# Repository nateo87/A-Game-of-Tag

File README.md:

# A Game of Tag
Here's the first genuine game project from David L Heiserman's 1978 book "How to Design & Build Your Own Custom TV Games". It's a very simple game where two player squares are moved around the screen. When one square touches another, both players disappear from the screen (it's up to you to decide who is "it"). Originally even less complex, I opted to add a little beep sound for when the tag occurs. The pitch of the beep can be set with a jumper on the upper-right side of the board.

It's easy for the player charcaters to fly off the screen - I recommend marking on your potentiometer knobs a sort of "starting position". Anyways, I encourage you to take a look into the book and tweak the designs. There's one addition the book recommends that would add "inertia" to the moving squares! Have fun, and please don't hesitate to reach out with questions.

You can just solder wires directly from your player control pots to the PCB, or you can use pinheaders and have wires going from the pots with crimped on molex connectors at the other end. 

<b> BOM </b>

Caps:<br>
100pf x 2<br>
3900pf x 2<br>
10nf x 4<br>
47nf x 2<br>
0.1uf x 9<br>

Elec. Caps:<br>
1uf x 2<br>
10uf x 1<br>

Resistors:<br>
470ohm x 4<br>
2.2k x 1<br>
3.3k x 2<br>
22k x 1<br>
33k x 2<br>
100k x 1<br>

Potentiometers:<br>
500k x 4

Diode:<br>
1N4148 x 1

Switch:<br>
6x6mm tact switch x 1

Pin headers:<br>
2x20 IDC male, 2.54mm pitch<br>
2x8 pin header, 2.54mm pitch<br>
1x3 pin header, 2.54mm pitch x 4<br>

ICs:<br>
74LS00 x 2<br>
74LS02<br>
74LS04<br>
74LS109<br>
LM555<br>
LM556 x 2

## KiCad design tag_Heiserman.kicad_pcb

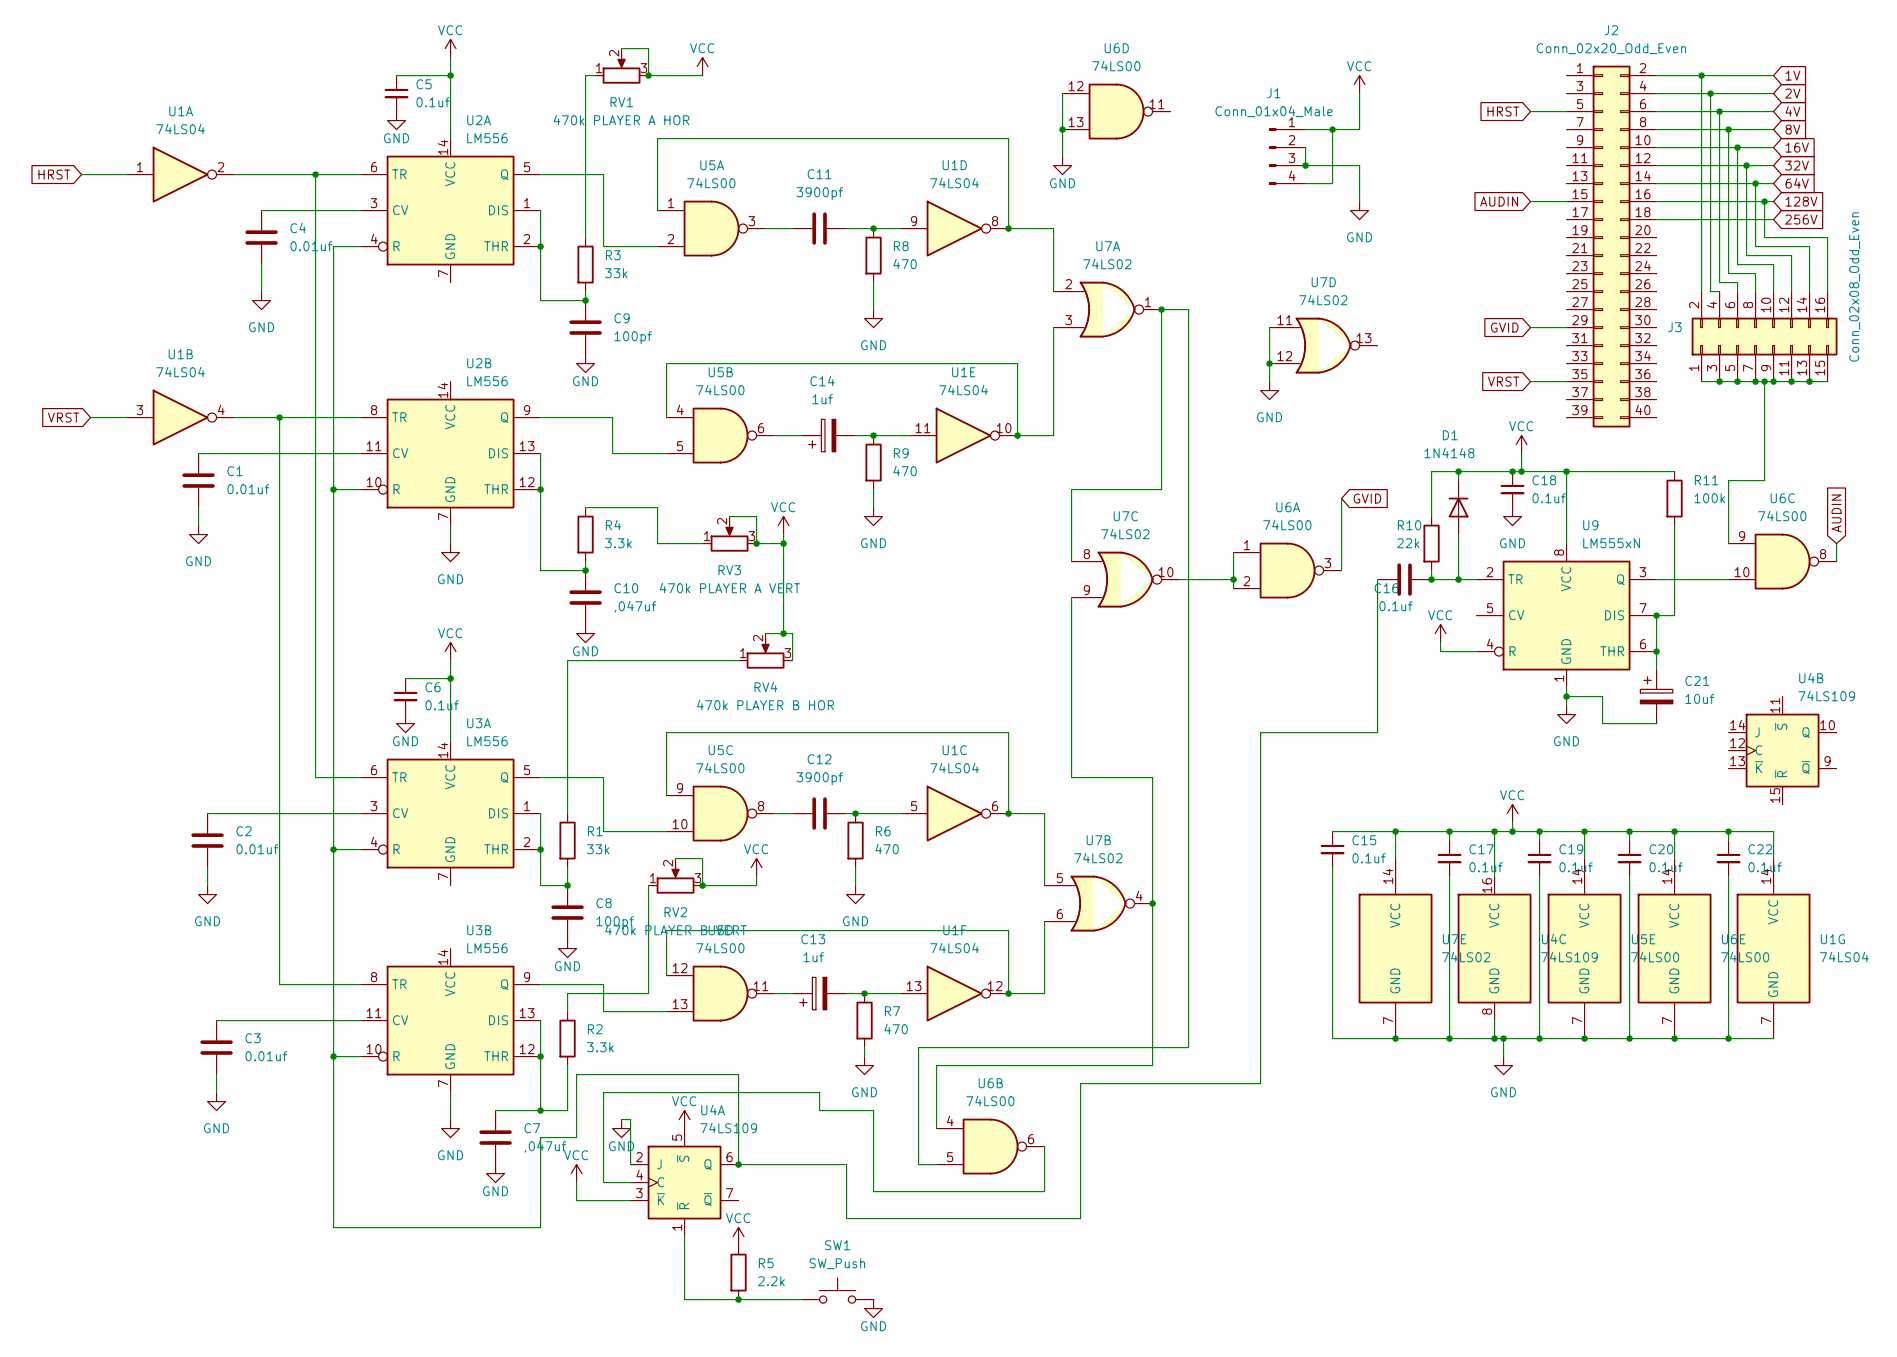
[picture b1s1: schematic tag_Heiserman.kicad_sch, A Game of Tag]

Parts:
C1, C2, C3, C4: 0.01uf; C_Disc_D3.4mm_W2.1mm_P2.50mm
C5, C6, C15, C16, C17, C18, C19, C20, C22: 0.1uf; C_Disc_D3.4mm_W2.1mm_P2.50mm
C7, C10: ,047uf; C_Disc_D3.4mm_W2.1mm_P2.50mm
C8, C9: 100pf; C_Disc_D3.4mm_W2.1mm_P2.50mm
C11, C12: 3900pf; C_Disc_D3.4mm_W2.1mm_P2.50mm
C13, C14: 1uf; CP_Radial_D5.0mm_P2.50mm
C21: 10uf; CP_Radial_D5.0mm_P2.50mm
D1: 1N4148; D_DO-35_SOD27_P7.62mm_Horizontal
J1: Conn_01x04_Male; JST_VH_B4P-VH-B_1x04_P3.96mm_Vertical
J2: Conn_02x20_Odd_Even; IDC-Header_2x20_P2.54mm_Vertical
J3: Conn_02x08_Odd_Even; PinHeader_2x08_P2.54mm_Vertical
R1, R3: 33k; R_Axial_DIN0204_L3.6mm_D1.6mm_P7.62mm_Horizontal
R2, R4: 3.3k; R_Axial_DIN0204_L3.6mm_D1.6mm_P7.62mm_Horizontal
R5: 2.2k; R_Axial_DIN0204_L3.6mm_D1.6mm_P7.62mm_Horizontal
R6, R7, R8, R9: 470; R_Axial_DIN0204_L3.6mm_D1.6mm_P7.62mm_Horizontal
R10: 22k; R_Axial_DIN0204_L3.6mm_D1.6mm_P7.62mm_Horizontal
R11: 100k; R_Axial_DIN0204_L3.6mm_D1.6mm_P7.62mm_Horizontal
RV1: 470k PLAYER A HOR; PinHeader_1x03_P2.54mm_Vertical
RV2: 470k PLAYER B VERT; PinHeader_1x03_P2.54mm_Vertical
RV3: 470k PLAYER A VERT; PinHeader_1x03_P2.54mm_Vertical
RV4: 470k PLAYER B HOR; PinHeader_1x03_P2.54mm_Vertical
SW1: SW_Push; SW_PUSH_6mm
U1: 74LS04; DIP-14_W7.62mm
U2, U3: LM556; DIP-14_W7.62mm
U4: 74LS109; DIP-16_W7.62mm
U5, U6: 74LS00; DIP-14_W7.62mm
U7: 74LS02; DIP-14_W7.62mm
U9: LM555xN; DIP-8_W7.62mm

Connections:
1V: J2.2, J3.2
2V: J2.4, J3.4
4V: J2.6, J3.6
8V: J2.8, J3.8
16V: J2.10, J3.10
32V: J2.12, J3.12
64V: J2.14, J3.14
128V: J2.16, J3.16
256V: J2.18
AUDIN: J2.15, U6.8
GND: C1.2, C2.2, C3.2, C4.2, C5.2, C6.2, C7.2, C8.2, C9.2, C10.2, C15.2, C17.2, C18.2, C19.2, C20.2, C21.2, C22.2, J1.2, J1.3, R6.2, R7.2, R8.2, R9.2, SW1.2, U1.7 (GND), U2.7 (GND), U3.7 (GND), U4.2 (J), U4.8 (GND), U5.7 (GND), U6.7 (GND), U6.12, U6.13, U7.7 (GND), U7.11, U7.12, U9.1 (GND)
GVID: J2.29, U6.3
HRST: J2.5, U1.1
unnamed: C1.1, U2.11 (CV)
unnamed: C2.1, U3.3 (CV)
unnamed: C3.1, U3.11 (CV)
unnamed: C4.1, U2.3 (CV)
unnamed: C7.1, R2.2, U3.12 (THR), U3.13 (DIS)
unnamed: C8.1, R1.2, U3.1 (DIS), U3.2 (THR)
unnamed: C9.1, R3.2, U2.1 (DIS), U2.2 (THR)
unnamed: C10.1, R4.2, U2.12 (THR), U2.13 (DIS)
unnamed: C11.1, R8.1, U1.9
unnamed: C11.2, U5.3
unnamed: C12.1, R6.1, U1.5
unnamed: C12.2, U5.8
unnamed: C13.1, U5.11
unnamed: C13.2, R7.1, U1.13
unnamed: C14.1, U5.6
unnamed: C14.2, R9.1, U1.11
unnamed: C16.1, D1.2 (A), R10.2, U9.2 (TR)
unnamed: C16.2, U2.4 (R), U2.10 (R), U3.4 (R), U3.10 (R), U4.6 (Q)
unnamed: C21.1, R11.2, U9.6 (THR), U9.7 (DIS)
unnamed: J3.1, J3.3, J3.5, J3.7, J3.9, J3.11, J3.13, J3.15, U6.9
unnamed: R1.1, RV4.1
unnamed: R2.1, RV2.1
unnamed: R3.1, RV1.1
unnamed: R4.1, RV3.1
unnamed: R5.2, SW1.1, U4.1 (~R)
unnamed: U1.2, U2.6 (TR), U3.6 (TR)
unnamed: U1.4, U2.8 (TR), U3.8 (TR)
unnamed: U1.6, U5.9, U7.5
unnamed: U1.8, U5.1, U7.2
unnamed: U1.10, U5.4, U7.3
unnamed: U1.12, U5.12, U7.6
unnamed: U2.5 (Q), U5.2
unnamed: U2.9 (Q), U5.5
unnamed: U3.5 (Q), U5.10
unnamed: U3.9 (Q), U5.13
unnamed: U4.4 (C), U6.6
unnamed: U6.1, U6.2, U7.10
unnamed: U6.4, U7.4, U7.9
unnamed: U6.5, U7.1, U7.8
unnamed: U6.10, U9.3 (Q)
VCC: C5.1, C6.1, C15.1, C17.1, C18.1, C19.1, C20.1, C22.1, D1.1 (K), J1.1, J1.4, R5.1, R10.1, R11.1, RV1.2, RV1.3, RV2.2, RV2.3, RV3.2, RV3.3, RV4.2, RV4.3, U1.14 (VCC), U2.14 (VCC), U3.14 (VCC), U4.3 (~K), U4.5 (~S), U4.16 (VCC), U5.14 (VCC), U6.14 (VCC), U7.14 (VCC), U9.4 (R), U9.8 (VCC)
VRST: J2.35, U1.3

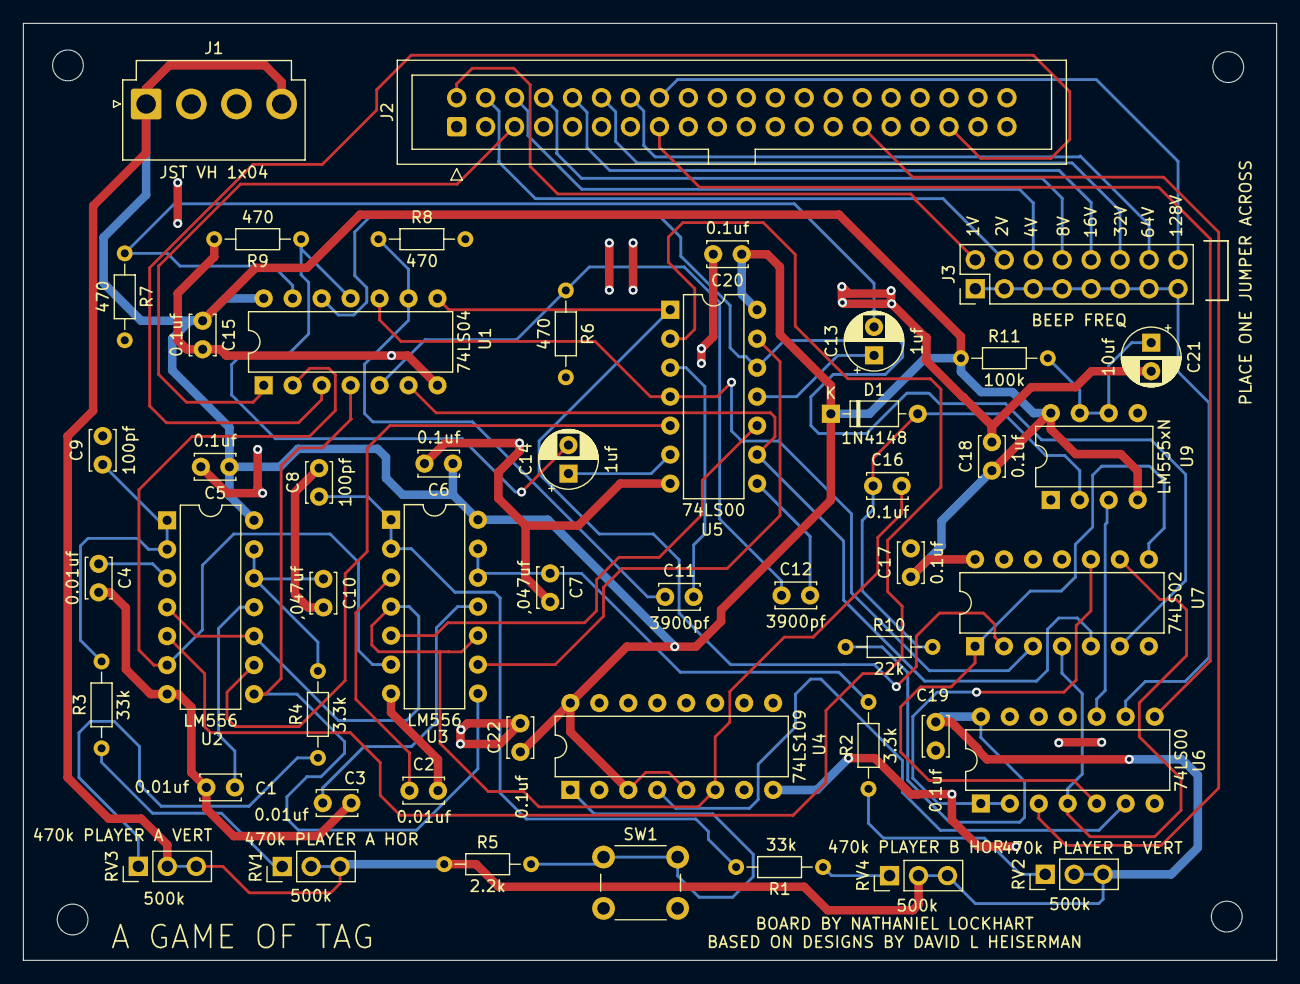
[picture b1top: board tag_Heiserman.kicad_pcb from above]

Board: 2 copper layers, 109.9 x 82.2 mm, 50 parts (0 on the bottom side), 54 nets.

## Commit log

2025-02-02 Rename tag_Heiserman.zip to gerber/tag_Heiserman.zip
2025-02-02 Rename tag_Heiserman.jpg to gallery/tag_Heiserman.jpg
